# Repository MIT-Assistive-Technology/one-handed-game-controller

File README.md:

# :video_game: **One-Handed Game Controller (Left-Handed)**

## :memo: **Instructions Overview**

⭐ **Please refer to [this handout](https://docs.google.com/document/d/1R1JeNCjT1L_K-hidx_33zdM9vNTuleeNFn41tkV1ZXg/edit?usp=sharing) for detailed instructions and materials.**

1. Download files
2. 3D print files
4. Print/Order PCBs
5. Solder Electronic Components
6. Upload code to the Arduino
7. Assemble

## :mag_right: Problem Statement
**Modern game controllers do not accommodate for one-handed users.**

After a stroke or injury, a person may lose some function in their body. Recreational products for the public are often made with the assumption that a person has full control of their body, which means that after permanent injuries, a person may become limited in their choice of hobbies.

Our codesigner, Susan Bibbins, suffers from chronic pain from fibromyalgia and has limited function in her right hand. She always wanted to play video games; however, modern controllers do not accomodate one-handed users.

Our team aims to develop a comfortable and accessible game controller designed specifically for one-handed users so that our codesigner can finally play video games that she has always wanted to try.

## 🔗 References

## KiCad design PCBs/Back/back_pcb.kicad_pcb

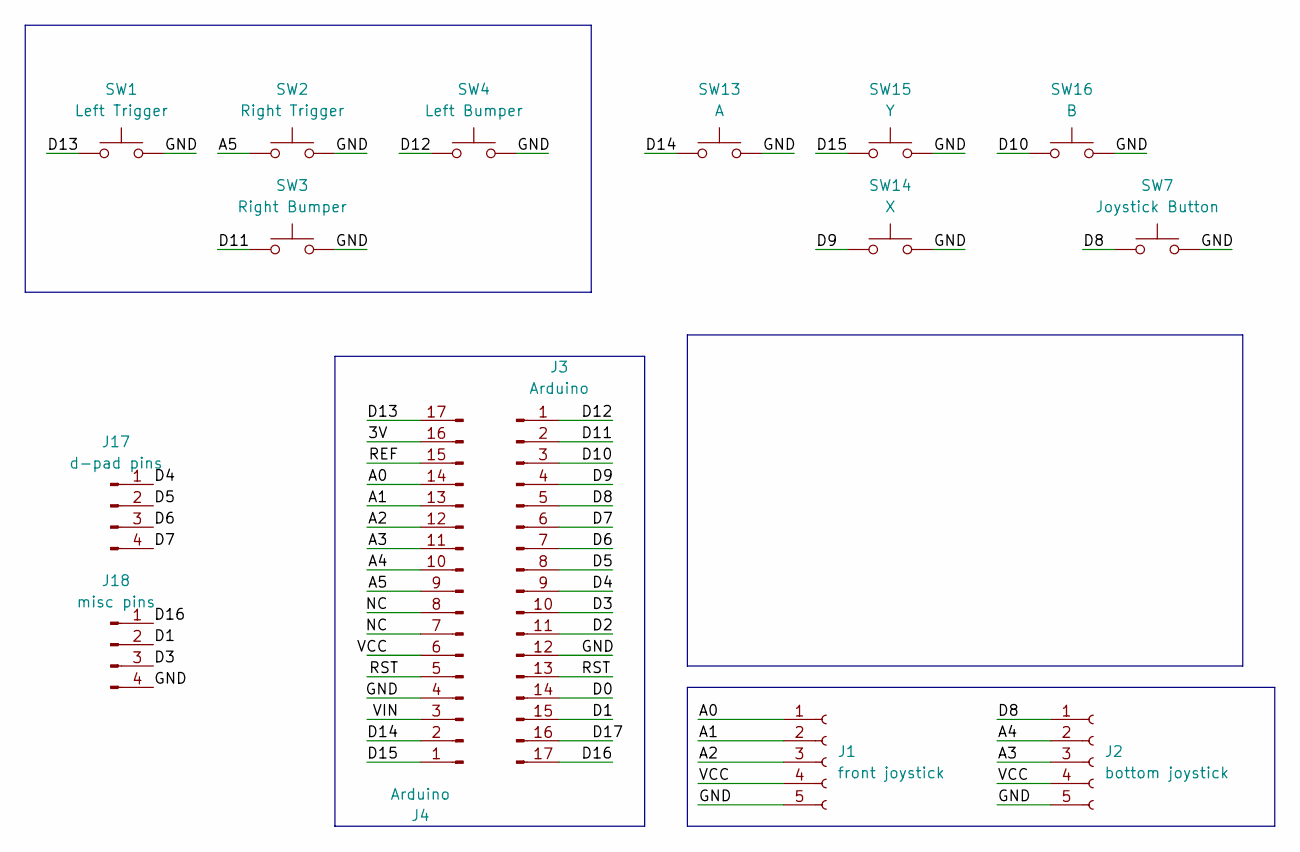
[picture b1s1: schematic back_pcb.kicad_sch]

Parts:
J1: front joystick; PinSocket_1x05_P2.54mm_Vertical
J2: bottom joystick; PinSocket_1x05_P2.54mm_Vertical
J3, J4: Arduino; PinSocket_1x17_P2.54mm_Vertical
J17: d-pad pins; PinSocket_1x04_P2.54mm_Vertical
J18: misc pins; PinSocket_1x04_P2.54mm_Vertical
SW1: Left Trigger; SW_BUTT-2
SW2: Right Trigger; SW_BUTT-2
SW3: Right Bumper; SW_BUTT-2
SW4: Left Bumper; SW_BUTT-2
SW7: Joystick Button; SW_BUTT-2
SW13: A; SW_BUTT-2
SW14: X; SW_BUTT-2
SW15: Y; SW_BUTT-2
SW16: B; SW_BUTT-2

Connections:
/3V: J4.16
/A0: J1.1, J4.14
/A1: J1.2, J4.13
/A2: J1.3, J4.12
/A3: J2.3, J4.11
/A4: J2.2, J4.10
/A5: J4.9, SW2.1
/D0: J3.14
/D1: J3.15, J18.2
/D2: J3.11
/D3: J3.10, J18.3
/D4: J3.9, J17.1
/D5: J3.8, J17.2
/D6: J3.7, J17.3
/D7: J3.6, J17.4
/D8: J2.1, J3.5, SW7.1
/D9: J3.4, SW14.1
/D10: J3.3, SW16.1
/D11: J3.2, SW3.1
/D12: J3.1, SW4.1
/D13: J4.17, SW1.1
/D14: J4.2, SW13.1
/D15: J4.1, SW15.1
/D16: J3.17, J18.1
/D17: J3.16
/GND: J1.5, J2.5, J3.12, J4.4, J18.4, SW1.2, SW2.2, SW3.2, SW4.2, SW7.2, SW13.2, SW14.2, SW15.2, SW16.2
/NC: J4.7, J4.8
/REF: J4.15
/RST: J3.13, J4.5
/VCC: J1.4, J2.4, J4.6
/VIN: J4.3

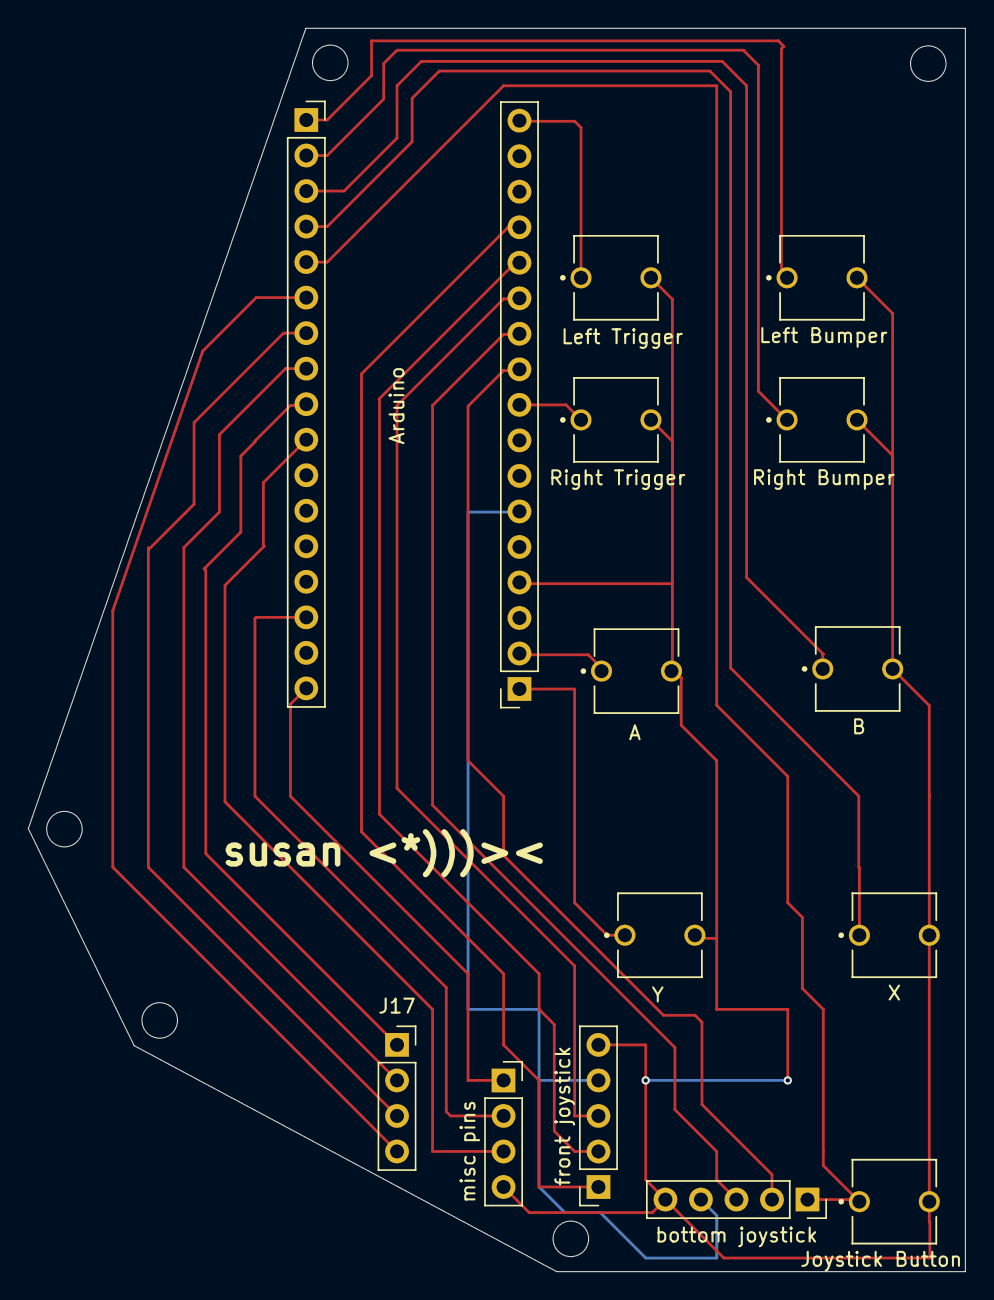
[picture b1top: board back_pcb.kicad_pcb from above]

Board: 2 copper layers, 67.0 x 88.9 mm, 15 parts (0 on the bottom side), 25 nets.

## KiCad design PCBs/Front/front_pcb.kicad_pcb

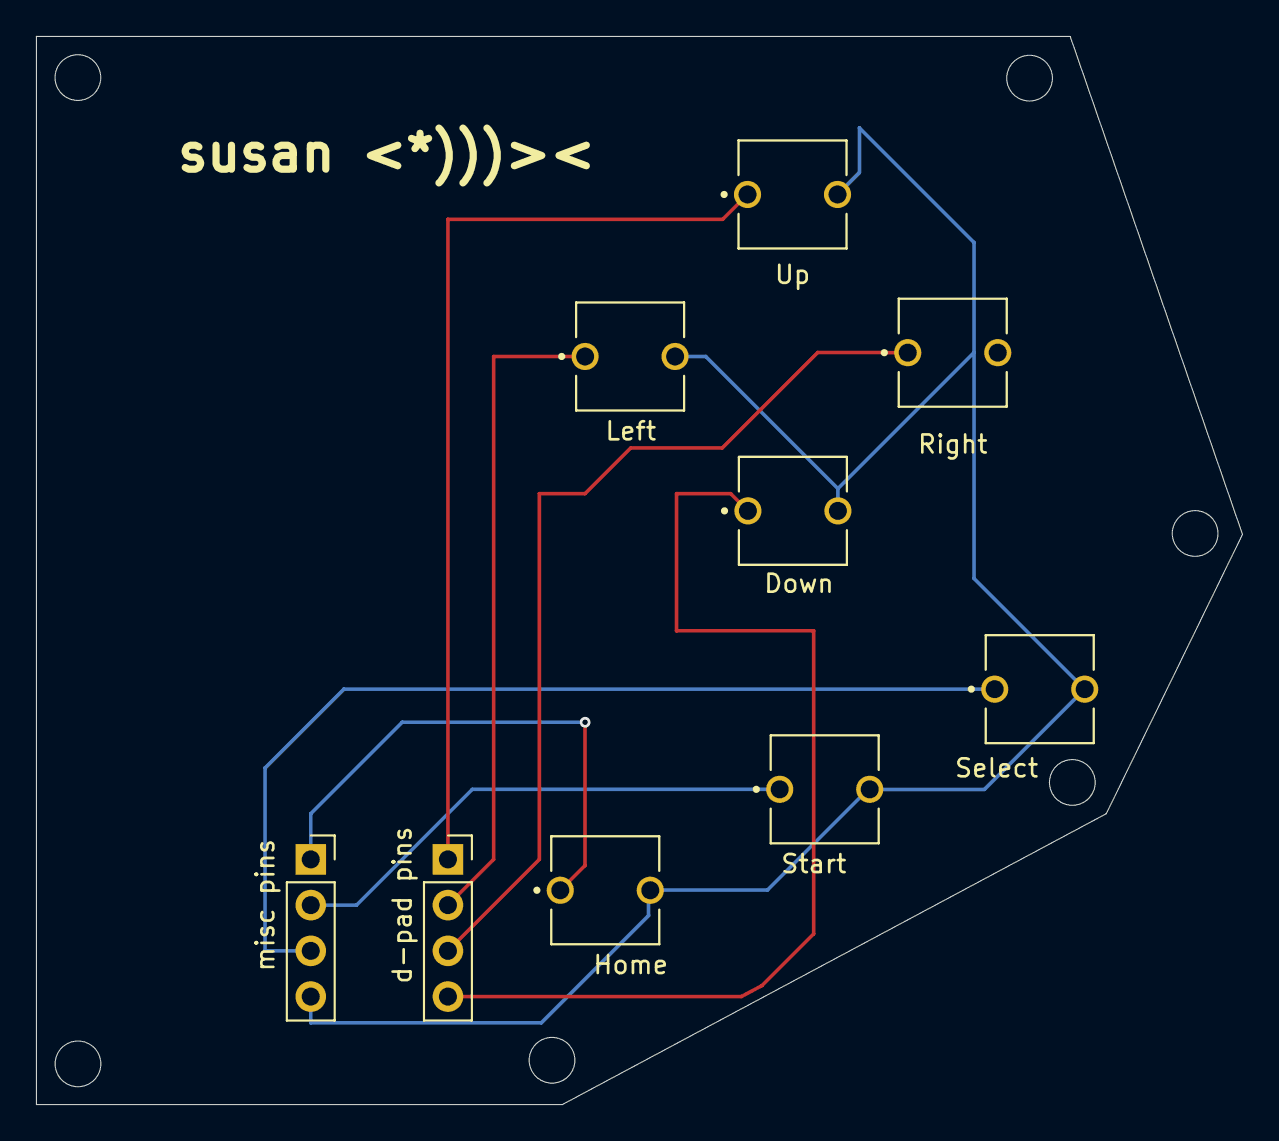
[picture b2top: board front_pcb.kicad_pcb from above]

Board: 2 copper layers, 67.0 x 59.3 mm, 9 parts (0 on the bottom side), 8 nets.

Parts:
J1: d-pad pins; PinSocket_1x04_P2.54mm_Vertical
J2: misc pins; PinSocket_1x04_P2.54mm_Vertical
SW1: Up; SW_BUTT-2
SW2: Down; SW_BUTT-2
SW3: Left; SW_BUTT-2
SW4: Right; SW_BUTT-2
SW6: Home; SW_BUTT-2
SW7: Start; SW_BUTT-2
SW8: Select; SW_BUTT-2

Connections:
/D0: J1.1, SW1.1
/D1: J2.3, SW8.1
/D2: J1.2, SW3.1
/D3: J1.3, SW4.1
/D4: J1.4, SW2.1
/D16: J2.1, SW6.1
/D17: J2.2, SW7.1
/GND: J2.4, SW1.2, SW2.2, SW3.2, SW4.2, SW6.2, SW7.2, SW8.2

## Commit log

2024-11-22 :tada: add project description
    - initialize readme
    - description in progress
2024-11-22 :sparkles: add PCBs
    - front PCB
    - back PCB
2024-11-22 :construction: add arduino code
    - code for arduino
2024-11-24 :sparkles: add base CADs
    - back face
    - backside
    - front face
    - front side
2024-11-24 :sparkles: add handle CAD
    - handle
2024-11-24 :sparkles: add mount CADs
    - 2 back PCB mounts
    - 2 front PCB mounts
2024-11-24 :truck: rename mounts
2025-06-02 🐛 add missing gnd connection
    - missing gnd connection to the misc pins
2025-08-24 ✨ add instruction document
2025-08-24 🐛 fix link
2025-08-24 :bug: fix link
